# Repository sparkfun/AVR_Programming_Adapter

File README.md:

**NOTE:** *This product has been retired from our catalog. We recommmend using the [SparkFun ISP Pogo Adapter](https://www.sparkfun.com/products/11591) as an alternative. If you are looking for more up-to-date info, please check out thef ollowing resource to see how other users are still hacking and improving on this product.*

* *[SparkFun Forum](https://forum.sparkfun.com/)*

AVR Programming Adapter
=======================

[
*SparkFun AVR Programming Adapter (BOB-08508)*](https://www.sparkfun.com/products/8508)

This pcb adapts 10-pin ISP programmers to the smaller 6-pin ISP connections. 
It can also be inserted directly into a breadboard with the 0.1" headers. 

Repository Contents
-------------------
* **/Hardware** - All Eagle design files (.brd, .sch)

License Information
-------------------
The hardware is released under [Creative Commons ShareAlike 4.0 International](https://creativecommons.org/licenses/by-sa/4.0/).

Distributed as-is; no warranty is given.

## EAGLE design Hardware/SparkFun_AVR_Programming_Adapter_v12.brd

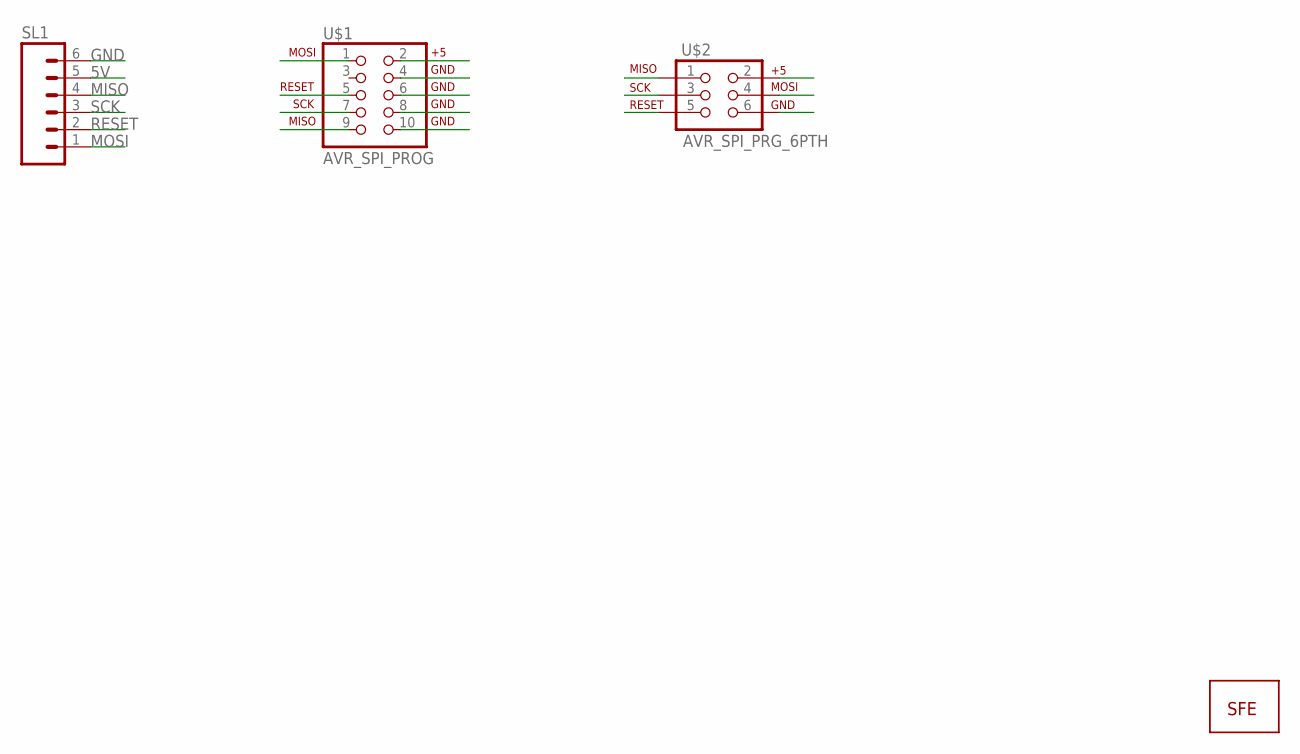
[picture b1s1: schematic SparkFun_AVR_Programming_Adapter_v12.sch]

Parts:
SL1: M06SIP; 1X06
U$1: AVR_SPI_PROG; AVR_ICSP
U$2: AVR_SPI_PRG_6PTH; 2X3
U$3: LOGO-SFENEW; SFE-NEW-WEBLOGO

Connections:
5V: SL1.5, U$1.2, U$2.2
GND: SL1.6, U$1.4, U$1.6, U$1.8, U$1.10, U$2.6
MISO: SL1.4, U$1.9, U$2.1
MOSI: SL1.1, U$1.1, U$2.4
RESET: SL1.2, U$1.5, U$2.5
SCK: SL1.3, U$1.7, U$2.3

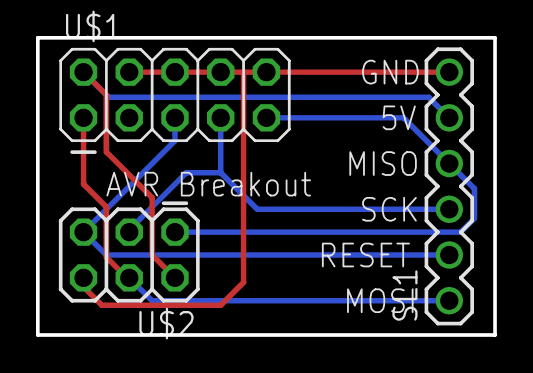
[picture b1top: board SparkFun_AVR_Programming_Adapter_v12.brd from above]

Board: 2 copper layers, 25.4 x 16.5 mm, 4 parts (1 on the bottom side), 6 nets.

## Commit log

2015-01-06 Initial hardware commit
